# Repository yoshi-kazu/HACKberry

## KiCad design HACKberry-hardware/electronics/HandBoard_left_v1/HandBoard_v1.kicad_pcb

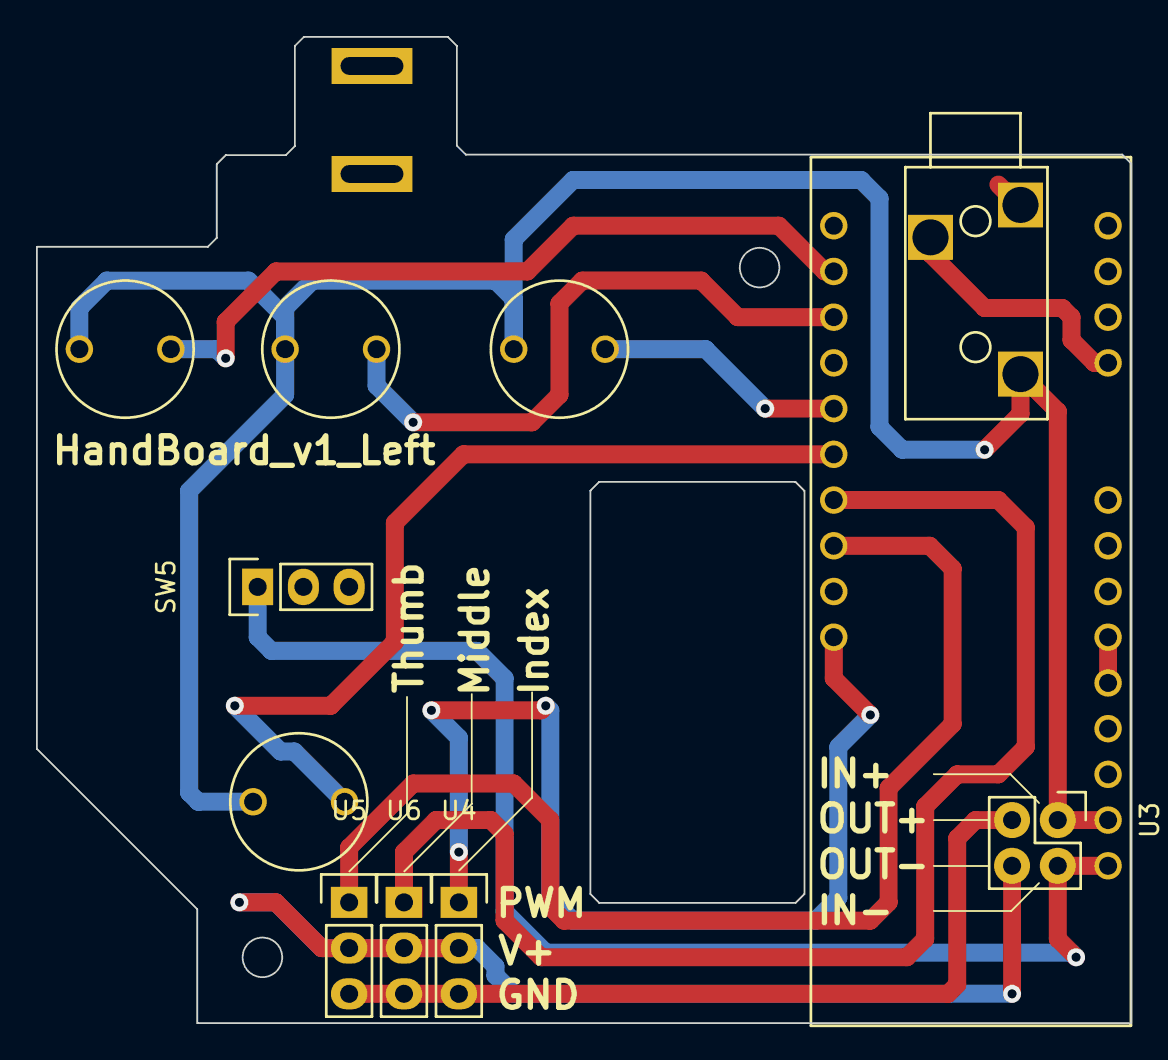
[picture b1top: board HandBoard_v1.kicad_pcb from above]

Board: 2 copper layers, 60.8 x 54.8 mm, 12 parts (0 on the bottom side), 12 nets.

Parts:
CON1: BARREL_JACK; MJ179PH
SW1:MAX1, SW2:MIN1, SW3:Thumb1, SW4:Middle1: SW_PUSH_SKRGAQD010; SKRGAQ0010
SW5: SWITCH_SS-12SDP2; Pin_Header_Straight_1x03
U1: 3-CONDUCTOR_MINIATUIRE_JACK_MJ-4535-3-RESCUE-Hand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; MINIATURE_JACK_MJ-4535-3
U2: Arduino_Micro
U3: Seed_Studio_Adjustable_DC/DC_Power_Converter_(1.2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; Pin_Header_Straight_2x02
U4: Servo_Motor_S03N; Pin_Header_Straight_1x03
U5, U6: Servo_Motor_ES08MD; Pin_Header_Straight_1x03

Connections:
/SW_MODE: SW3:Thumb1.2, U2.8
/SW_OPEN: SW2:MIN1.2, U2.10
/SW_PINCH: SW4:Middle1.2, U2.7
unnamed: SW1:MAX1.1, SW2:MIN1.1, SW3:Thumb1.1, SW4:Middle1.1, U1.1, U2.GND, U3.2
unnamed: SW1:MAX1.2, U2.11
unnamed: SW5.1, U2.VIN, U3.1
unnamed: U1.4, U2.A0
unnamed: U2.3, U4.1
unnamed: U2.5, U5.1
unnamed: U2.6, U6.1
unnamed: U3.3, U4.3, U5.3, U6.3
unnamed: U3.4, U4.2, U5.2, U6.2

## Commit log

2016-06-03 MJ179PHを追加したがkicadさん馬鹿なので数字が一致してるかどうかの判定ができずにschとbrdの整合を取れないらしい
2016-06-06 DCDCのピン配置，大きさを変更．配線を引き直し，おそらく完成．
2016-06-06 センサの電源を5Vに変更
